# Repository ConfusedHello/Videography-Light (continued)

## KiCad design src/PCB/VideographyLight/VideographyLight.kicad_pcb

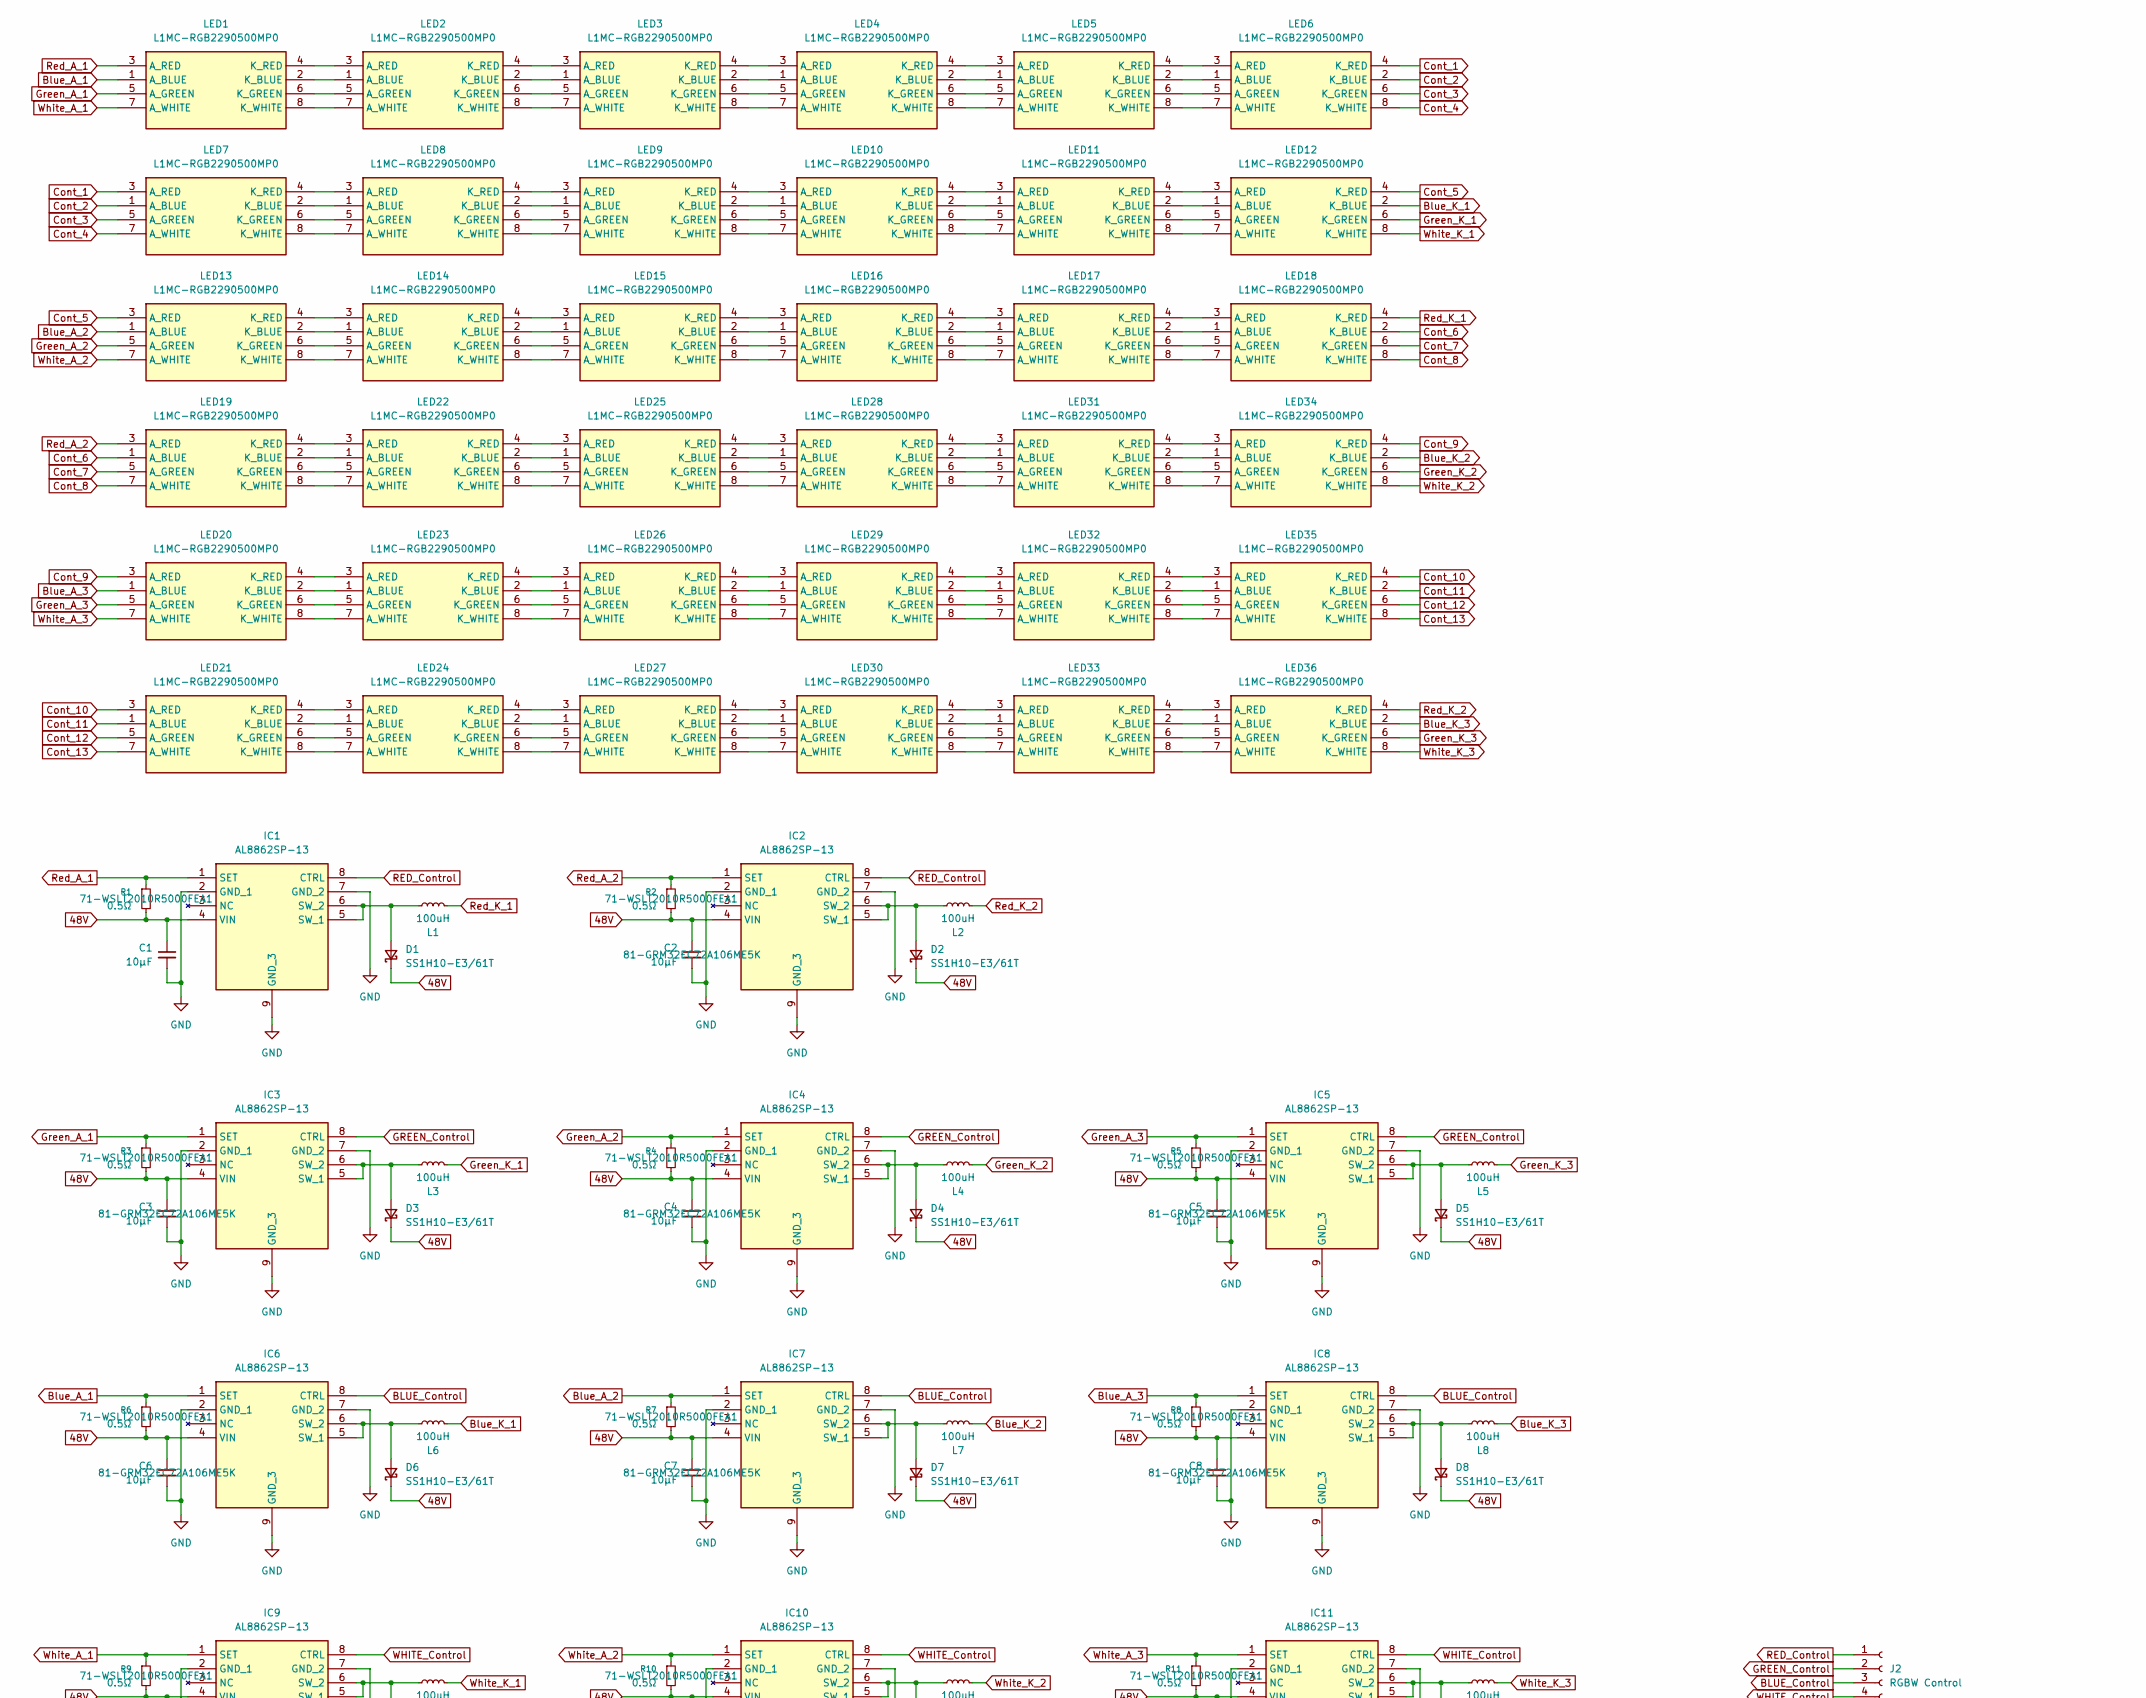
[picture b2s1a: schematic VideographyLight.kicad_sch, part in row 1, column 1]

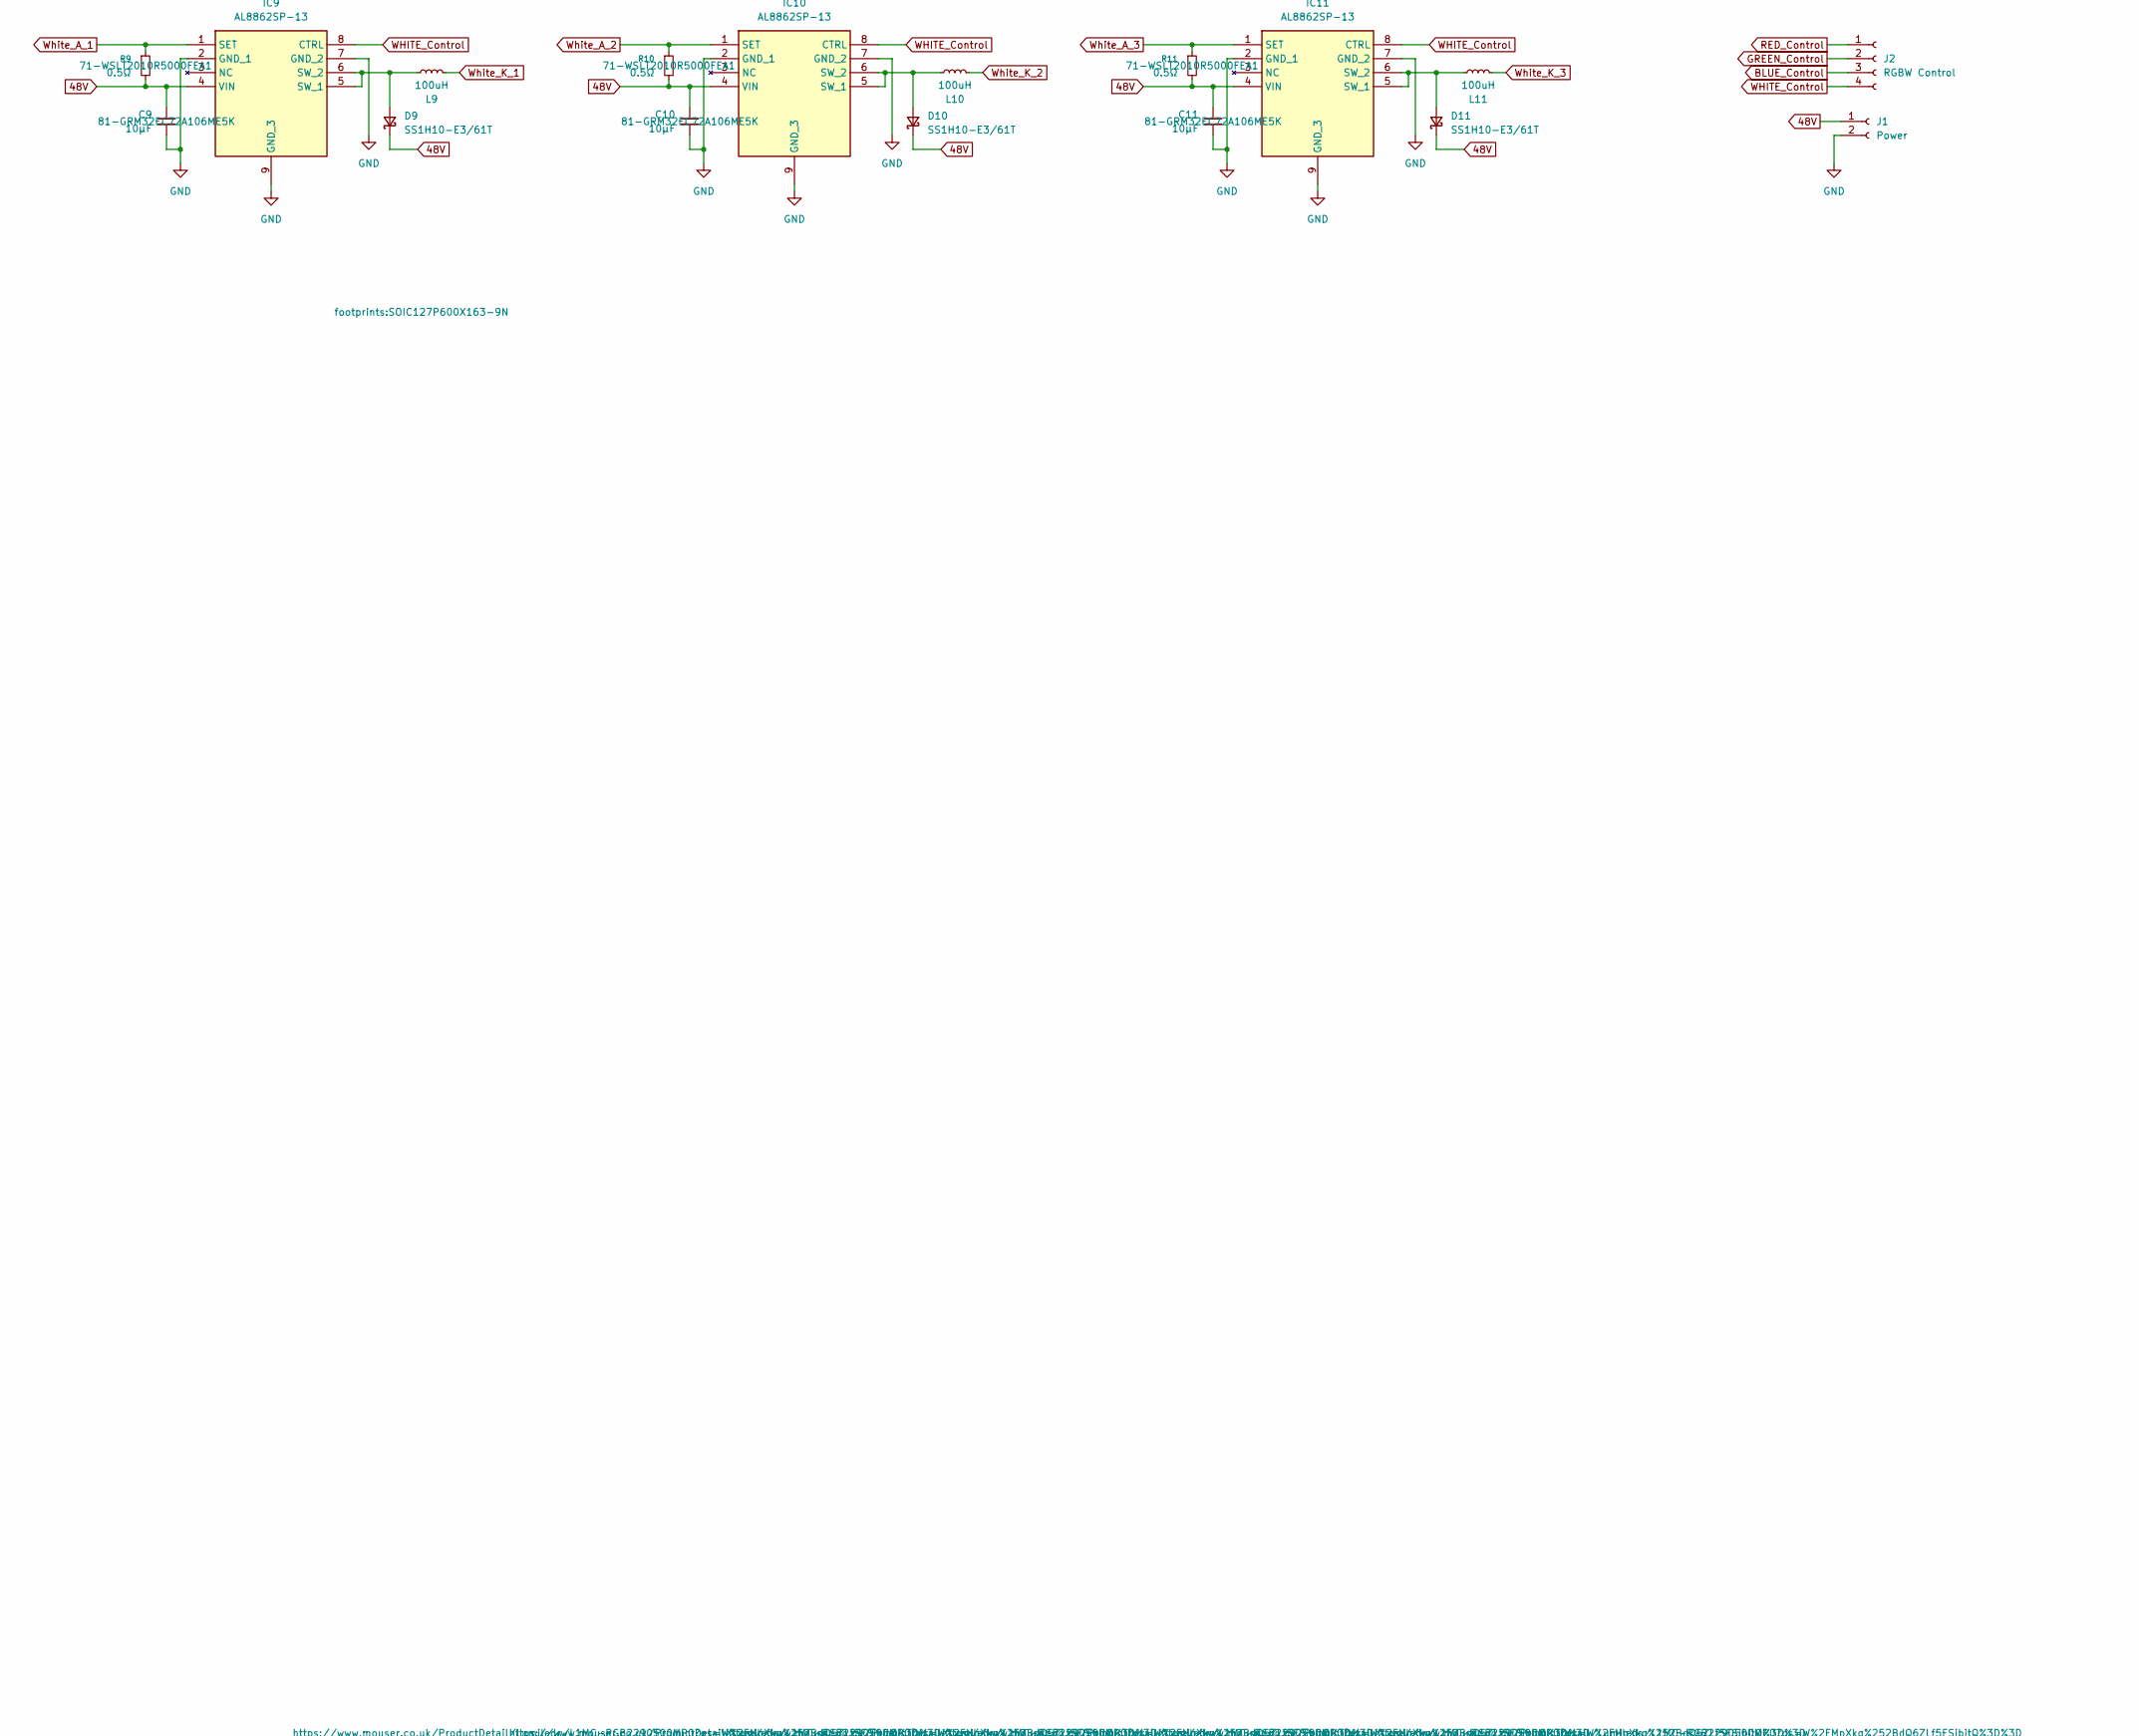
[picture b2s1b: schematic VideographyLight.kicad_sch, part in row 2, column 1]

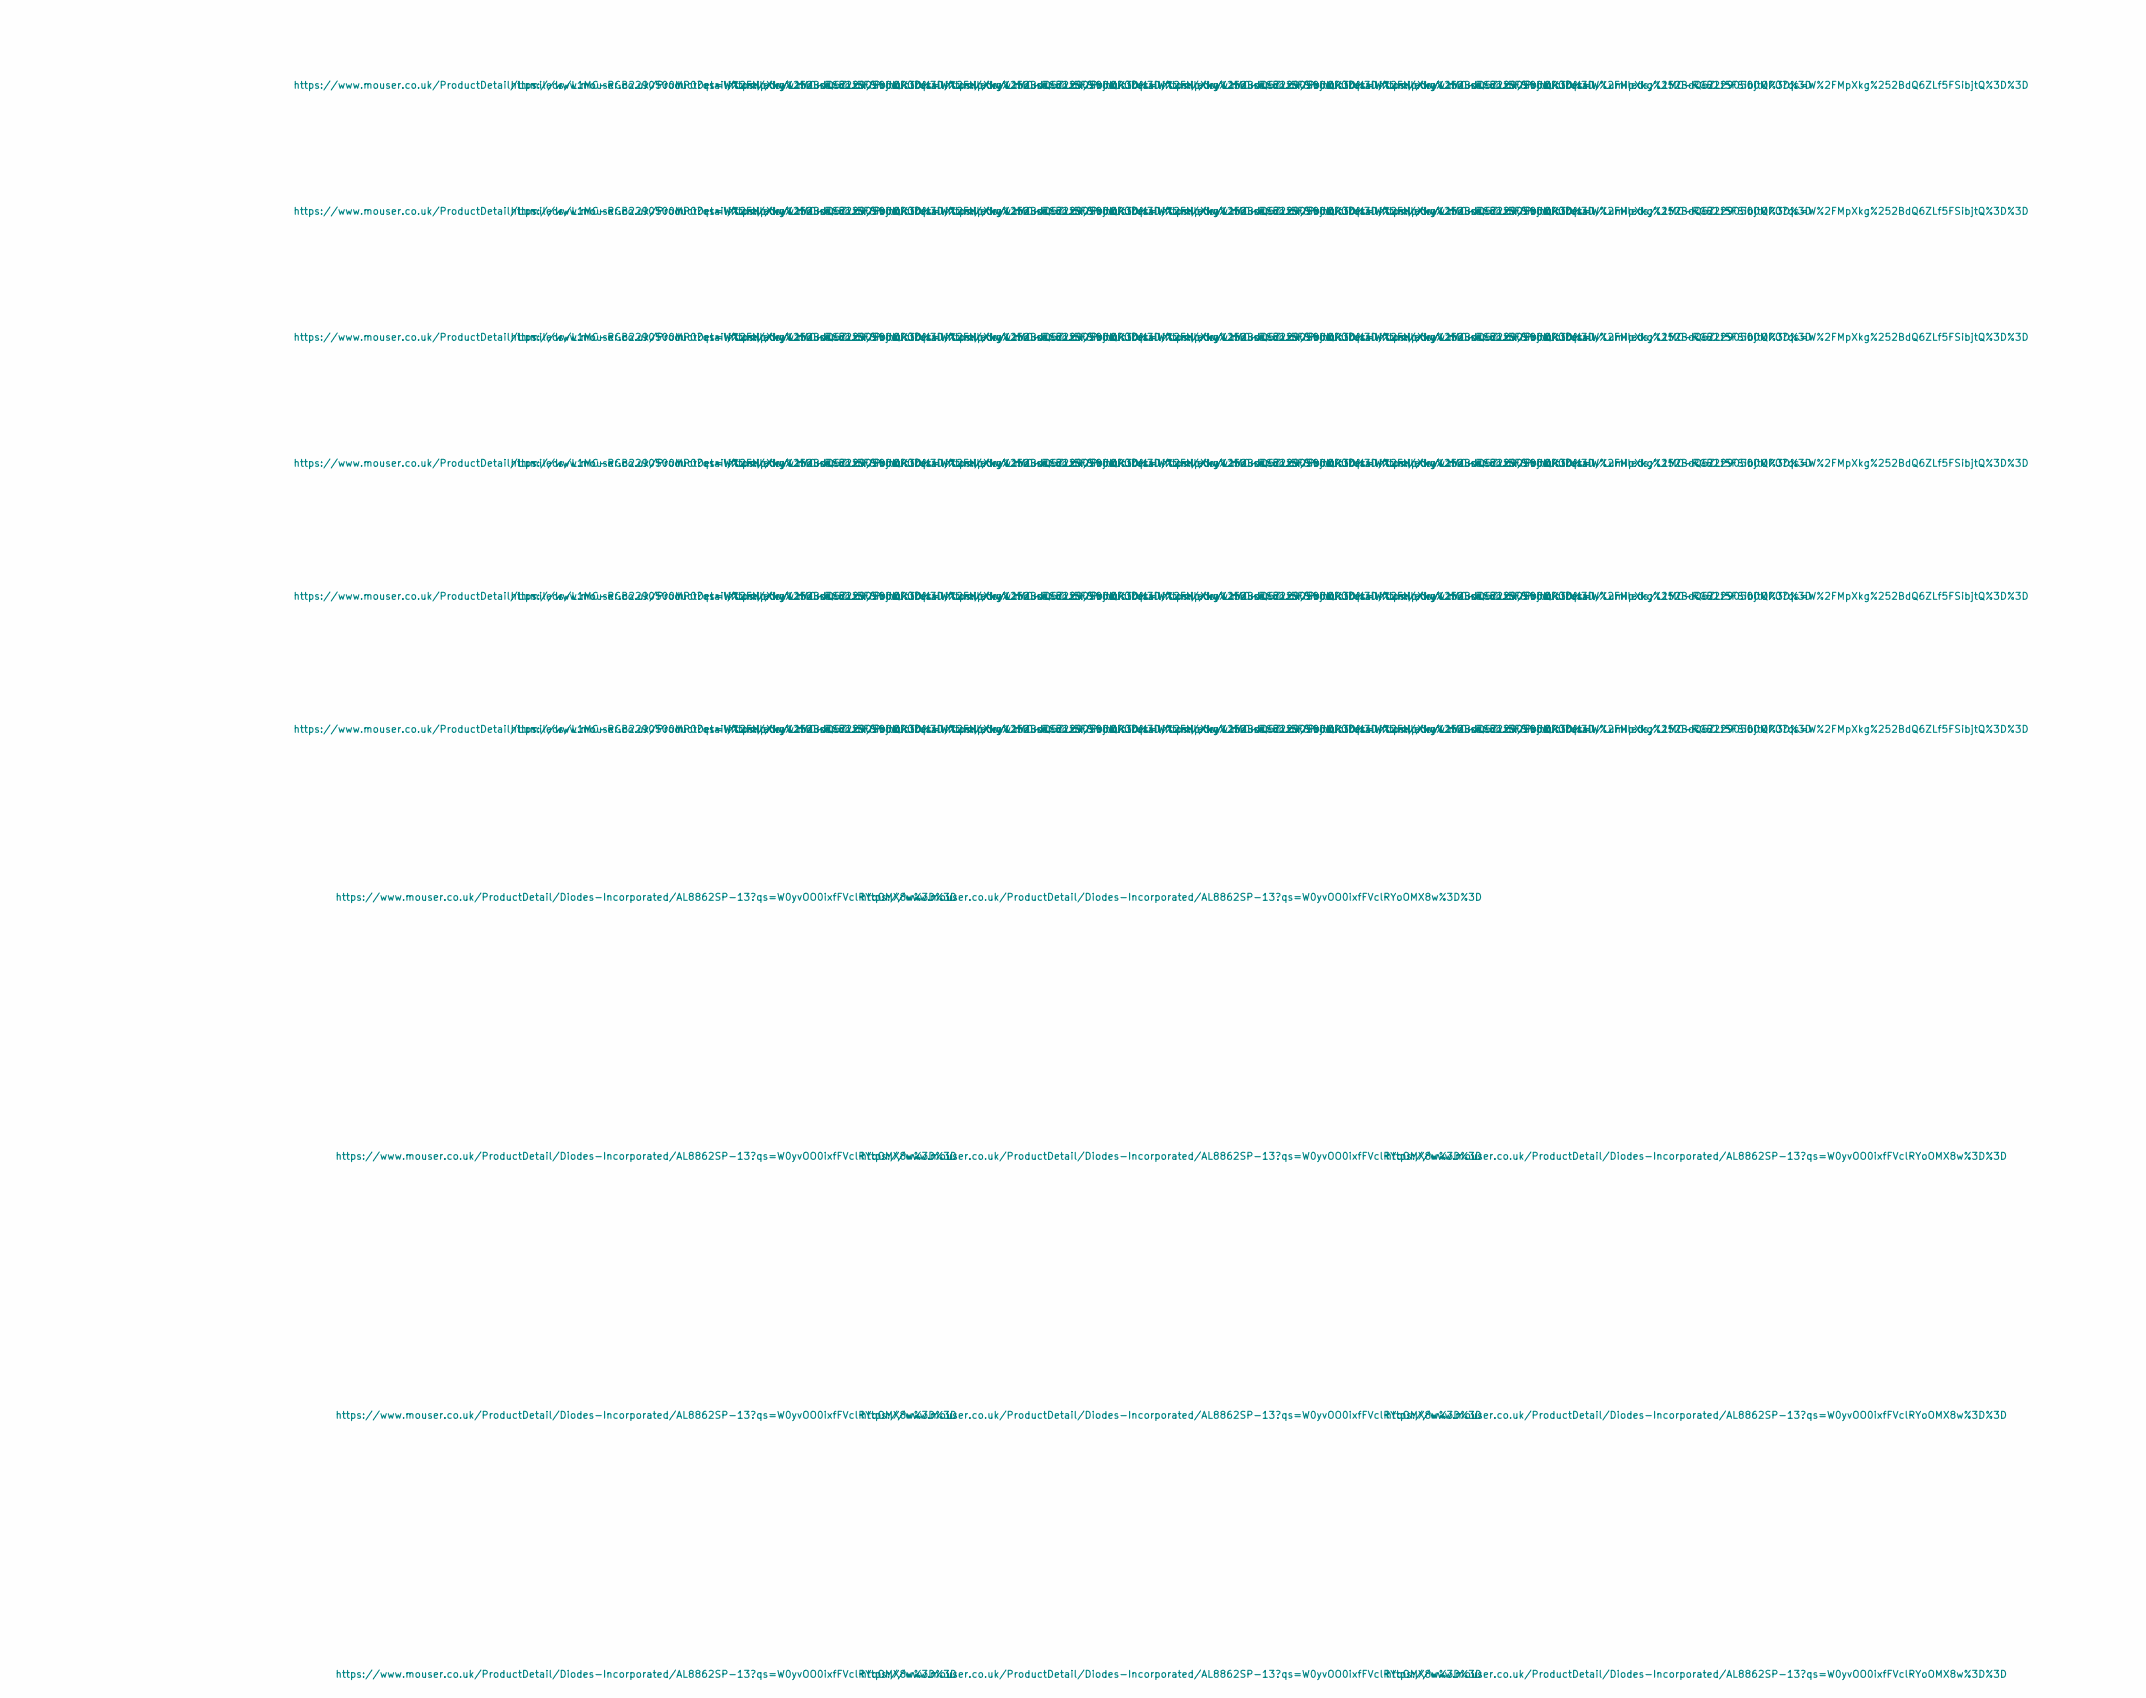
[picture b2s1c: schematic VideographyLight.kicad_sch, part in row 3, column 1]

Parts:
C1, C2, C3, C4, C5, C6, C7, C8, C9, C10, C11: 10μF; C_1210_3225Metric_Pad1.33x2.70mm_HandSolder; Mouser Part Number 81-GRM32EC72A106ME5K
D1, D2, D3, D4, D5, D6, D7, D8, D9, D10, D11: SS1H10-E3/61T; DIOM5127X229N; Mouser Part Number 625-SS1H10-E3
IC1, IC2, IC3, IC4, IC5, IC6, IC7, IC8, IC9, IC10, IC11: AL8862SP-13; SOIC127P600X163-9N; Mouser Part Number 621-AL8862SP-13
J1: Power; TerminalBlock_Phoenix_MKDS-1,5-2-5.08_1x02_P5.08mm_Horizont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; Mouser Part Number 179-TB0012-508-02GR
J2: RGBW Control; TerminalBlock_Phoenix_MKDS-1,5-4-5.08_1x04_P5.08mm_Horizont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; Mouser Part Number 179-TB0012-508-04GR
L1, L2, L3, L4, L5, L6, L7, L8, L9, L10, L11: 100uH; INDPM120120X600N; Mouser Part Number 710-7447706101
LED1, LED2, LED3, LED4, LED5, LED6, LED7, LED8, LED9, LED10, LED11, LED12, LED13, LED14, LED15, LED16, LED17, LED18, LED19, LED20, LED21, LED22, LED23, LED24, LED25, LED26, LED27, LED28, LED29, LED30, LED31, LED32, LED33, LED34, LED35, LED36: L1MC-RGB2290500MP0; L1MCRGB2290500MP0; Mouser Part Number 997-L1MCRGB2295MP0
R1, R2, R3, R4, R5, R6, R7, R8, R9, R10, R11: 0.5Ω; R_2010_5025Metric_Pad1.40x2.65mm_HandSolder; Mouser Part Number 71-WSLT2010R5000FEA1

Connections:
48V: C1.1, C2.1, C3.1, C4.1, C5.1, C6.1, C7.1, C8.1, C9.1, C10.1, C11.1, D1.1 (K), D2.1 (K), D3.1 (K), D4.1 (K), D5.1 (K), D6.1 (K), D7.1 (K), D8.1 (K), D9.1 (K), D10.1 (K), D11.1 (K), IC1.4 (VIN), IC2.4 (VIN), IC3.4 (VIN), IC4.4 (VIN), IC5.4 (VIN), IC6.4 (VIN), IC7.4 (VIN), IC8.4 (VIN), IC9.4 (VIN), IC10.4 (VIN), IC11.4 (VIN), J1.1, R1.2, R2.2, R3.2, R4.2, R5.2, R6.2, R7.2, R8.2, R9.2, R10.2, R11.2
BLUE_Control: IC6.8 (CTRL), IC7.8 (CTRL), IC8.8 (CTRL), J2.3
Blue_A_1: IC6.1 (SET), LED1.1 (A_BLUE), R6.1
Blue_A_2: IC7.1 (SET), LED13.1 (A_BLUE), R7.1
Blue_A_3: IC8.1 (SET), LED20.1 (A_BLUE), R8.1
Blue_K_1: L6.1, LED12.2 (K_BLUE)
Blue_K_2: L7.1, LED34.2 (K_BLUE)
Blue_K_3: L8.1, LED36.2 (K_BLUE)
Cont_1: LED6.4 (K_RED), LED7.3 (A_RED), LED7.9 (A_RED_2)
Cont_2: LED6.2 (K_BLUE), LED7.1 (A_BLUE)
Cont_3: LED6.6 (K_GREEN), LED7.5 (A_GREEN)
Cont_4: LED6.8 (K_WHITE), LED7.7 (A_WHITE)
Cont_5: LED12.4 (K_RED), LED13.3 (A_RED), LED13.9 (A_RED_2)
Cont_6: LED18.2 (K_BLUE), LED19.1 (A_BLUE)
Cont_7: LED18.6 (K_GREEN), LED19.5 (A_GREEN)
Cont_8: LED18.8 (K_WHITE), LED19.7 (A_WHITE)
Cont_9: LED20.3 (A_RED), LED20.9 (A_RED_2), LED34.4 (K_RED)
Cont_10: LED21.3 (A_RED), LED21.9 (A_RED_2), LED35.4 (K_RED)
Cont_11: LED21.1 (A_BLUE), LED35.2 (K_BLUE)
Cont_12: LED21.5 (A_GREEN), LED35.6 (K_GREEN)
Cont_13: LED21.7 (A_WHITE), LED35.8 (K_WHITE)
GND: C1.2, C2.2, C3.2, C4.2, C5.2, C6.2, C7.2, C8.2, C9.2, C10.2, C11.2, IC1.2 (GND_1), IC1.7 (GND_2), IC1.9 (GND_3), IC2.2 (GND_1), IC2.7 (GND_2), IC2.9 (GND_3), IC3.2 (GND_1), IC3.7 (GND_2), IC3.9 (GND_3), IC4.2 (GND_1), IC4.7 (GND_2), IC4.9 (GND_3), IC5.2 (GND_1), IC5.7 (GND_2), IC5.9 (GND_3), IC6.2 (GND_1), IC6.7 (GND_2), IC6.9 (GND_3), IC7.2 (GND_1), IC7.7 (GND_2), IC7.9 (GND_3), IC8.2 (GND_1), IC8.7 (GND_2), IC8.9 (GND_3), IC9.2 (GND_1), IC9.7 (GND_2), IC9.9 (GND_3), IC10.2 (GND_1), IC10.7 (GND_2), IC10.9 (GND_3), IC11.2 (GND_1), IC11.7 (GND_2), IC11.9 (GND_3), J1.2
GREEN_Control: IC3.8 (CTRL), IC4.8 (CTRL), IC5.8 (CTRL), J2.2
Green_A_1: IC3.1 (SET), LED1.5 (A_GREEN), R3.1
Green_A_2: IC4.1 (SET), LED13.5 (A_GREEN), R4.1
Green_A_3: IC5.1 (SET), LED20.5 (A_GREEN), R5.1
Green_K_1: L3.1, LED12.6 (K_GREEN)
Green_K_2: L4.1, LED34.6 (K_GREEN)
Green_K_3: L5.1, LED36.6 (K_GREEN)
unnamed: D1.2 (A), IC1.5 (SW_1), IC1.6 (SW_2), L1.2
unnamed: D2.2 (A), IC2.5 (SW_1), IC2.6 (SW_2), L2.2
unnamed: D3.2 (A), IC3.5 (SW_1), IC3.6 (SW_2), L3.2
unnamed: D4.2 (A), IC4.5 (SW_1), IC4.6 (SW_2), L4.2
unnamed: D5.2 (A), IC5.5 (SW_1), IC5.6 (SW_2), L5.2
unnamed: D6.2 (A), IC6.5 (SW_1), IC6.6 (SW_2), L6.2
unnamed: D7.2 (A), IC7.5 (SW_1), IC7.6 (SW_2), L7.2
unnamed: D8.2 (A), IC8.5 (SW_1), IC8.6 (SW_2), L8.2
unnamed: D9.2 (A), IC9.5 (SW_1), IC9.6 (SW_2), L9.2
unnamed: D10.2 (A), IC10.5 (SW_1), IC10.6 (SW_2), L10.2
unnamed: D11.2 (A), IC11.5 (SW_1), IC11.6 (SW_2), L11.2
unnamed: LED1.2 (K_BLUE), LED2.1 (A_BLUE)
unnamed: LED1.6 (K_GREEN), LED2.5 (A_GREEN)
unnamed: LED1.4 (K_RED), LED2.3 (A_RED), LED2.9 (A_RED_2)
unnamed: LED1.8 (K_WHITE), LED2.7 (A_WHITE)
unnamed: LED2.2 (K_BLUE), LED3.1 (A_BLUE)
unnamed: LED2.6 (K_GREEN), LED3.5 (A_GREEN)
unnamed: LED2.4 (K_RED), LED3.3 (A_RED), LED3.9 (A_RED_2)
unnamed: LED2.8 (K_WHITE), LED3.7 (A_WHITE)
unnamed: LED3.2 (K_BLUE), LED4.1 (A_BLUE)
unnamed: LED3.6 (K_GREEN), LED4.5 (A_GREEN)
unnamed: LED3.4 (K_RED), LED4.3 (A_RED), LED4.9 (A_RED_2)
unnamed: LED3.8 (K_WHITE), LED4.7 (A_WHITE)
unnamed: LED4.2 (K_BLUE), LED5.1 (A_BLUE)
unnamed: LED4.6 (K_GREEN), LED5.5 (A_GREEN)
unnamed: LED4.4 (K_RED), LED5.3 (A_RED), LED5.9 (A_RED_2)
unnamed: LED4.8 (K_WHITE), LED5.7 (A_WHITE)
unnamed: LED5.2 (K_BLUE), LED6.1 (A_BLUE)
unnamed: LED5.6 (K_GREEN), LED6.5 (A_GREEN)
unnamed: LED5.4 (K_RED), LED6.3 (A_RED), LED6.9 (A_RED_2)
unnamed: LED5.8 (K_WHITE), LED6.7 (A_WHITE)
unnamed: LED7.2 (K_BLUE), LED8.1 (A_BLUE)
unnamed: LED7.6 (K_GREEN), LED8.5 (A_GREEN)
unnamed: LED7.4 (K_RED), LED8.3 (A_RED), LED8.9 (A_RED_2)
unnamed: LED7.8 (K_WHITE), LED8.7 (A_WHITE)
unnamed: LED8.2 (K_BLUE), LED9.1 (A_BLUE)
unnamed: LED8.6 (K_GREEN), LED9.5 (A_GREEN)
unnamed: LED8.4 (K_RED), LED9.3 (A_RED), LED9.9 (A_RED_2)
unnamed: LED8.8 (K_WHITE), LED9.7 (A_WHITE)
unnamed: LED9.2 (K_BLUE), LED10.1 (A_BLUE)
unnamed: LED9.6 (K_GREEN), LED10.5 (A_GREEN)
unnamed: LED9.4 (K_RED), LED10.3 (A_RED), LED10.9 (A_RED_2)
unnamed: LED9.8 (K_WHITE), LED10.7 (A_WHITE)
unnamed: LED10.2 (K_BLUE), LED11.1 (A_BLUE)
unnamed: LED10.6 (K_GREEN), LED11.5 (A_GREEN)
unnamed: LED10.4 (K_RED), LED11.3 (A_RED), LED11.9 (A_RED_2)
unnamed: LED10.8 (K_WHITE), LED11.7 (A_WHITE)
unnamed: LED11.2 (K_BLUE), LED12.1 (A_BLUE)
unnamed: LED11.6 (K_GREEN), LED12.5 (A_GREEN)
unnamed: LED11.4 (K_RED), LED12.3 (A_RED), LED12.9 (A_RED_2)
unnamed: LED11.8 (K_WHITE), LED12.7 (A_WHITE)
unnamed: LED13.2 (K_BLUE), LED14.1 (A_BLUE)
unnamed: LED13.6 (K_GREEN), LED14.5 (A_GREEN)
unnamed: LED13.4 (K_RED), LED14.3 (A_RED), LED14.9 (A_RED_2)
unnamed: LED13.8 (K_WHITE), LED14.7 (A_WHITE)
unnamed: LED14.2 (K_BLUE), LED15.1 (A_BLUE)
unnamed: LED14.6 (K_GREEN), LED15.5 (A_GREEN)
unnamed: LED14.4 (K_RED), LED15.3 (A_RED), LED15.9 (A_RED_2)
unnamed: LED14.8 (K_WHITE), LED15.7 (A_WHITE)
unnamed: LED15.2 (K_BLUE), LED16.1 (A_BLUE)
unnamed: LED15.6 (K_GREEN), LED16.5 (A_GREEN)
unnamed: LED15.4 (K_RED), LED16.3 (A_RED), LED16.9 (A_RED_2)
unnamed: LED15.8 (K_WHITE), LED16.7 (A_WHITE)
unnamed: LED16.2 (K_BLUE), LED17.1 (A_BLUE)
unnamed: LED16.6 (K_GREEN), LED17.5 (A_GREEN)
unnamed: LED16.4 (K_RED), LED17.3 (A_RED), LED17.9 (A_RED_2)
unnamed: LED16.8 (K_WHITE), LED17.7 (A_WHITE)
unnamed: LED17.2 (K_BLUE), LED18.1 (A_BLUE)
unnamed: LED17.6 (K_GREEN), LED18.5 (A_GREEN)
unnamed: LED17.4 (K_RED), LED18.3 (A_RED), LED18.9 (A_RED_2)
unnamed: LED17.8 (K_WHITE), LED18.7 (A_WHITE)
unnamed: LED19.2 (K_BLUE), LED22.1 (A_BLUE)
unnamed: LED19.6 (K_GREEN), LED22.5 (A_GREEN)
unnamed: LED19.4 (K_RED), LED22.3 (A_RED), LED22.9 (A_RED_2)
unnamed: LED19.8 (K_WHITE), LED22.7 (A_WHITE)
unnamed: LED20.2 (K_BLUE), LED23.1 (A_BLUE)
unnamed: LED20.6 (K_GREEN), LED23.5 (A_GREEN)
unnamed: LED20.4 (K_RED), LED23.3 (A_RED), LED23.9 (A_RED_2)
unnamed: LED20.8 (K_WHITE), LED23.7 (A_WHITE)
unnamed: LED21.2 (K_BLUE), LED24.1 (A_BLUE)
unnamed: LED21.6 (K_GREEN), LED24.5 (A_GREEN)
unnamed: LED21.4 (K_RED), LED24.3 (A_RED), LED24.9 (A_RED_2)
unnamed: LED21.8 (K_WHITE), LED24.7 (A_WHITE)
unnamed: LED22.2 (K_BLUE), LED25.1 (A_BLUE)
unnamed: LED22.6 (K_GREEN), LED25.5 (A_GREEN)
unnamed: LED22.4 (K_RED), LED25.3 (A_RED), LED25.9 (A_RED_2)
unnamed: LED22.8 (K_WHITE), LED25.7 (A_WHITE)
unnamed: LED23.2 (K_BLUE), LED26.1 (A_BLUE)
unnamed: LED23.6 (K_GREEN), LED26.5 (A_GREEN)
unnamed: LED23.4 (K_RED), LED26.3 (A_RED), LED26.9 (A_RED_2)
unnamed: LED23.8 (K_WHITE), LED26.7 (A_WHITE)
unnamed: LED24.2 (K_BLUE), LED27.1 (A_BLUE)
unnamed: LED24.6 (K_GREEN), LED27.5 (A_GREEN)
unnamed: LED24.4 (K_RED), LED27.3 (A_RED), LED27.9 (A_RED_2)
unnamed: LED24.8 (K_WHITE), LED27.7 (A_WHITE)
unnamed: LED25.2 (K_BLUE), LED28.1 (A_BLUE)
unnamed: LED25.6 (K_GREEN), LED28.5 (A_GREEN)
unnamed: LED25.4 (K_RED), LED28.3 (A_RED), LED28.9 (A_RED_2)
unnamed: LED25.8 (K_WHITE), LED28.7 (A_WHITE)
unnamed: LED26.2 (K_BLUE), LED29.1 (A_BLUE)
unnamed: LED26.6 (K_GREEN), LED29.5 (A_GREEN)
unnamed: LED26.4 (K_RED), LED29.3 (A_RED), LED29.9 (A_RED_2)
unnamed: LED26.8 (K_WHITE), LED29.7 (A_WHITE)
unnamed: LED27.2 (K_BLUE), LED30.1 (A_BLUE)
unnamed: LED27.6 (K_GREEN), LED30.5 (A_GREEN)
unnamed: LED27.4 (K_RED), LED30.3 (A_RED), LED30.9 (A_RED_2)
unnamed: LED27.8 (K_WHITE), LED30.7 (A_WHITE)
unnamed: LED28.2 (K_BLUE), LED31.1 (A_BLUE)
unnamed: LED28.6 (K_GREEN), LED31.5 (A_GREEN)
unnamed: LED28.4 (K_RED), LED31.3 (A_RED), LED31.9 (A_RED_2)
unnamed: LED28.8 (K_WHITE), LED31.7 (A_WHITE)
unnamed: LED29.2 (K_BLUE), LED32.1 (A_BLUE)
unnamed: LED29.6 (K_GREEN), LED32.5 (A_GREEN)
unnamed: LED29.4 (K_RED), LED32.3 (A_RED), LED32.9 (A_RED_2)
unnamed: LED29.8 (K_WHITE), LED32.7 (A_WHITE)
unnamed: LED30.2 (K_BLUE), LED33.1 (A_BLUE)
unnamed: LED30.6 (K_GREEN), LED33.5 (A_GREEN)
unnamed: LED30.4 (K_RED), LED33.3 (A_RED), LED33.9 (A_RED_2)
unnamed: LED30.8 (K_WHITE), LED33.7 (A_WHITE)
unnamed: LED31.2 (K_BLUE), LED34.1 (A_BLUE)
unnamed: LED31.6 (K_GREEN), LED34.5 (A_GREEN)
unnamed: LED31.4 (K_RED), LED34.3 (A_RED), LED34.9 (A_RED_2)
unnamed: LED31.8 (K_WHITE), LED34.7 (A_WHITE)
unnamed: LED32.2 (K_BLUE), LED35.1 (A_BLUE)
unnamed: LED32.6 (K_GREEN), LED35.5 (A_GREEN)
unnamed: LED32.4 (K_RED), LED35.3 (A_RED), LED35.9 (A_RED_2)
unnamed: LED32.8 (K_WHITE), LED35.7 (A_WHITE)
unnamed: LED33.2 (K_BLUE), LED36.1 (A_BLUE)
unnamed: LED33.6 (K_GREEN), LED36.5 (A_GREEN)
unnamed: LED33.4 (K_RED), LED36.3 (A_RED), LED36.9 (A_RED_2)
unnamed: LED33.8 (K_WHITE), LED36.7 (A_WHITE)
RED_Control: IC1.8 (CTRL), IC2.8 (CTRL), J2.1
Red_A_1: IC1.1 (SET), LED1.3 (A_RED), LED1.9 (A_RED_2), R1.1
Red_A_2: IC2.1 (SET), LED19.3 (A_RED), LED19.9 (A_RED_2), R2.1
Red_K_1: L1.1, LED18.4 (K_RED)
Red_K_2: L2.1, LED36.4 (K_RED)
WHITE_Control: IC9.8 (CTRL), IC10.8 (CTRL), IC11.8 (CTRL), J2.4
White_A_1: IC9.1 (SET), LED1.7 (A_WHITE), R9.1
White_A_2: IC10.1 (SET), LED13.7 (A_WHITE), R10.1
White_A_3: IC11.1 (SET), LED20.7 (A_WHITE), R11.1
White_K_1: L9.1, LED12.8 (K_WHITE)
White_K_2: L10.1, LED34.8 (K_WHITE)
White_K_3: L11.1, LED36.8 (K_WHITE)

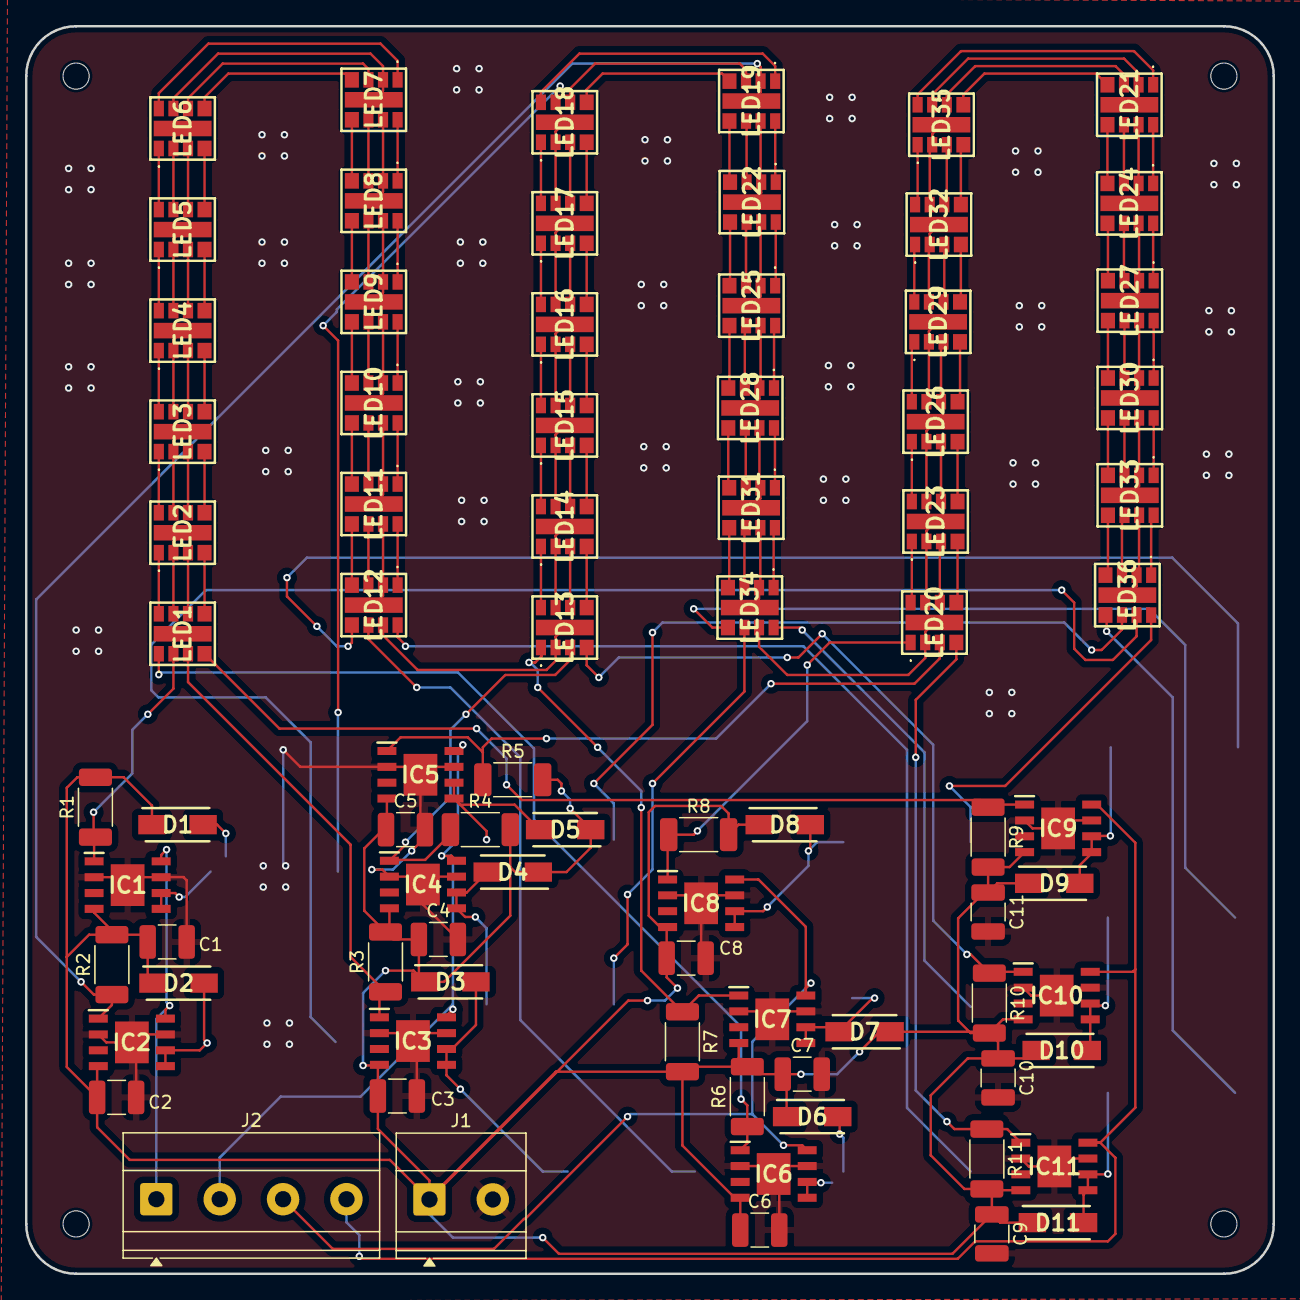
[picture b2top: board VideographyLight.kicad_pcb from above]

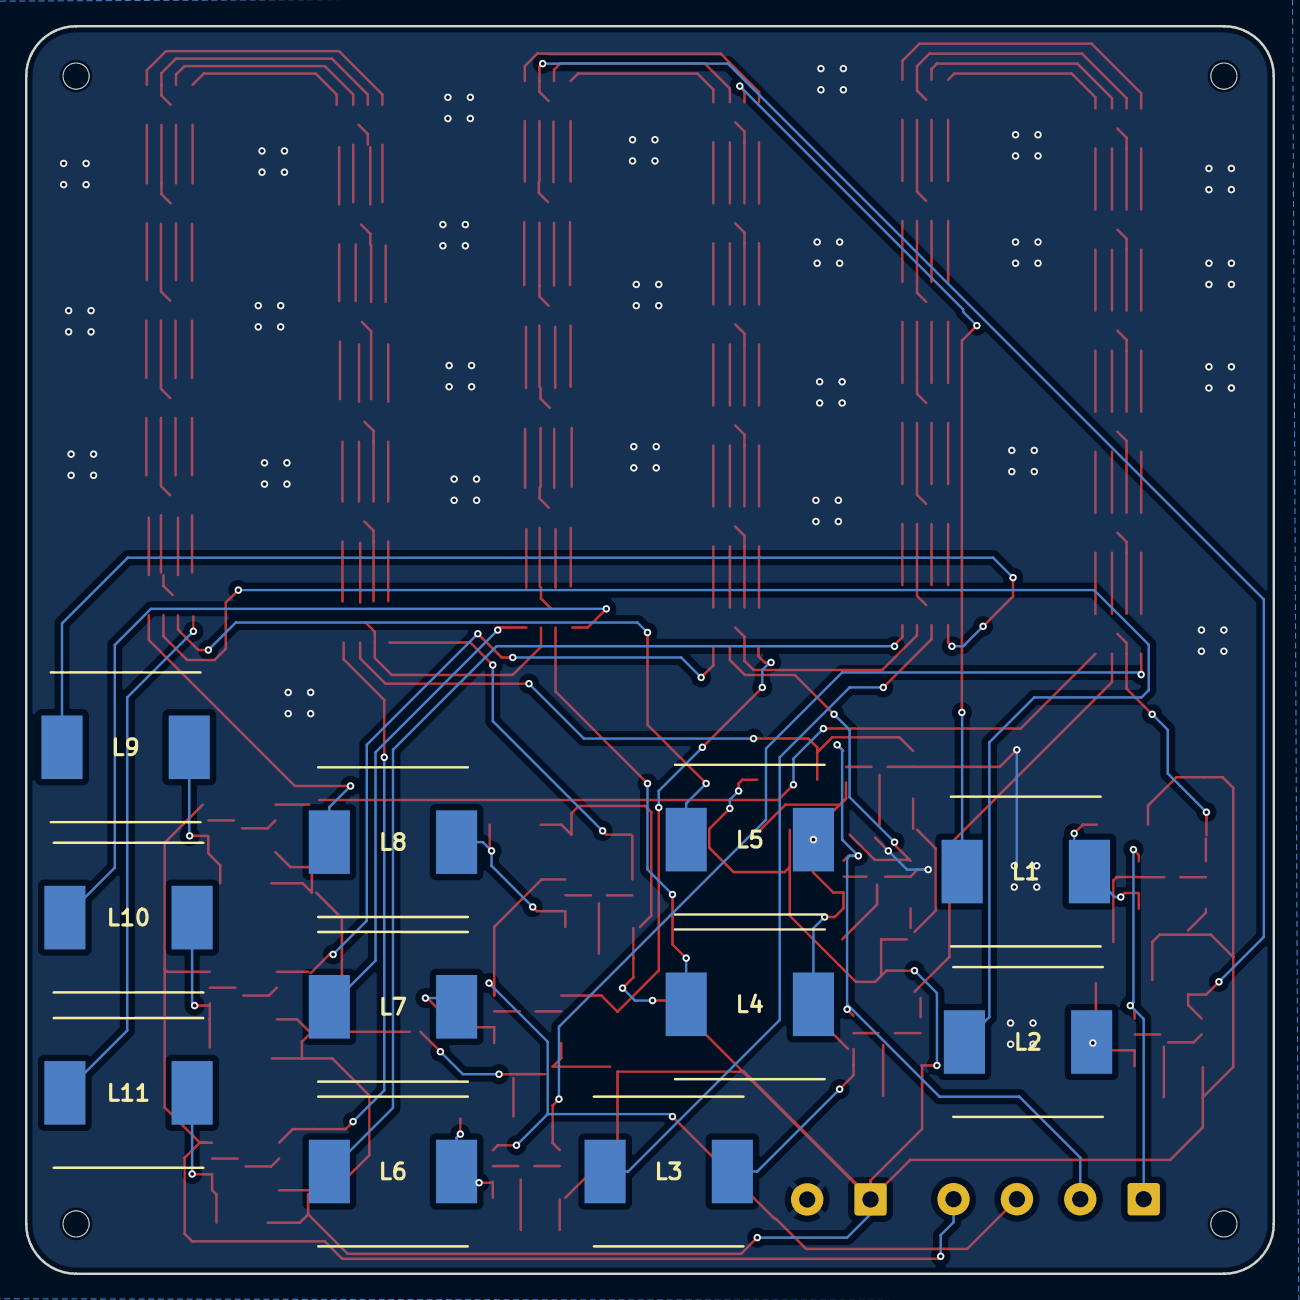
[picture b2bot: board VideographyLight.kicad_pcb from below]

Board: 2 copper layers, 100.0 x 100.0 mm, 93 parts (11 on the bottom side), 172 nets.

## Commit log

2025-07-01 Initial Upload
2025-07-01 Update JOURNAL
2025-07-02 Add Kicad .gitignore
2025-07-02 Upload Control Board
    Add initial project files and setup.
2025-07-02 Rearrange Files
2025-07-02 Add Control Board Exports
2025-07-02 Upload software
2025-07-03 Push model for CAD
2025-07-07 Upload Light PCB
2025-07-07 Add 3D Print Case STEP Files
2025-07-07 Update BOM export for Control Board
2025-07-07 Update BOM
2025-07-07 Update Case Design
2025-07-07 Upload completed BOM
2025-07-07 Add Wiring Diagram to README
2025-07-07 Add screen location and power hole to case design
2025-07-07 Fix BOM
2025-07-08 Add case journal entry
2025-07-08 Add case sketch image
2025-07-08 Add images to journal
2025-07-08 Remove old .f3d files
2025-07-08 Upload images for silkscreen
2025-07-08 Move image in incorrect folder
2025-07-08 Final JOURNAL update before submission
2025-07-08 Add case render image
2025-07-08 Add banner
2025-07-08 Upscale banner
2025-07-08 Finalise README
2025-07-08 Finalise PCB and upload gerbers
2025-07-08 Update banner
2025-07-08 Add CAD to README
